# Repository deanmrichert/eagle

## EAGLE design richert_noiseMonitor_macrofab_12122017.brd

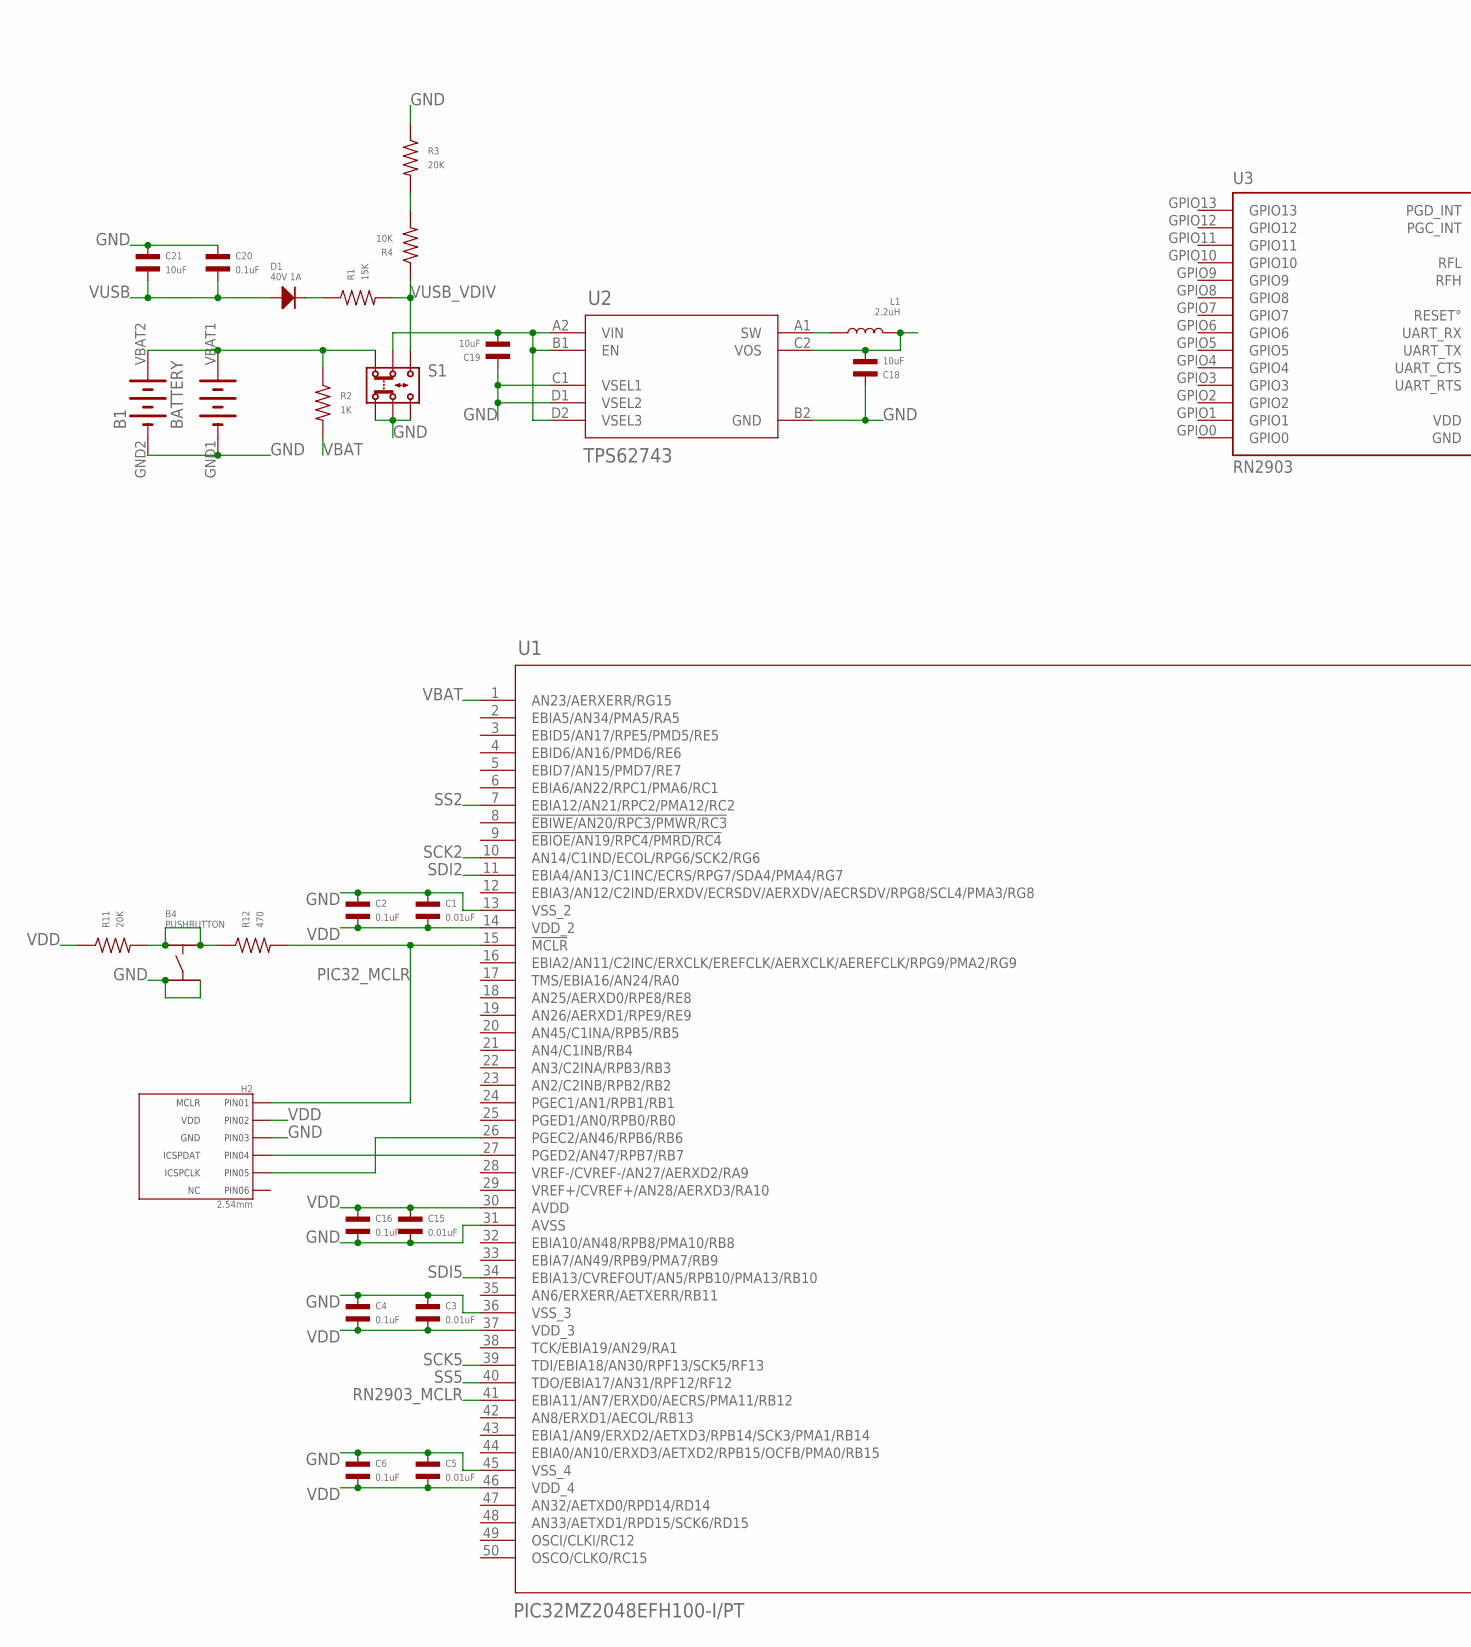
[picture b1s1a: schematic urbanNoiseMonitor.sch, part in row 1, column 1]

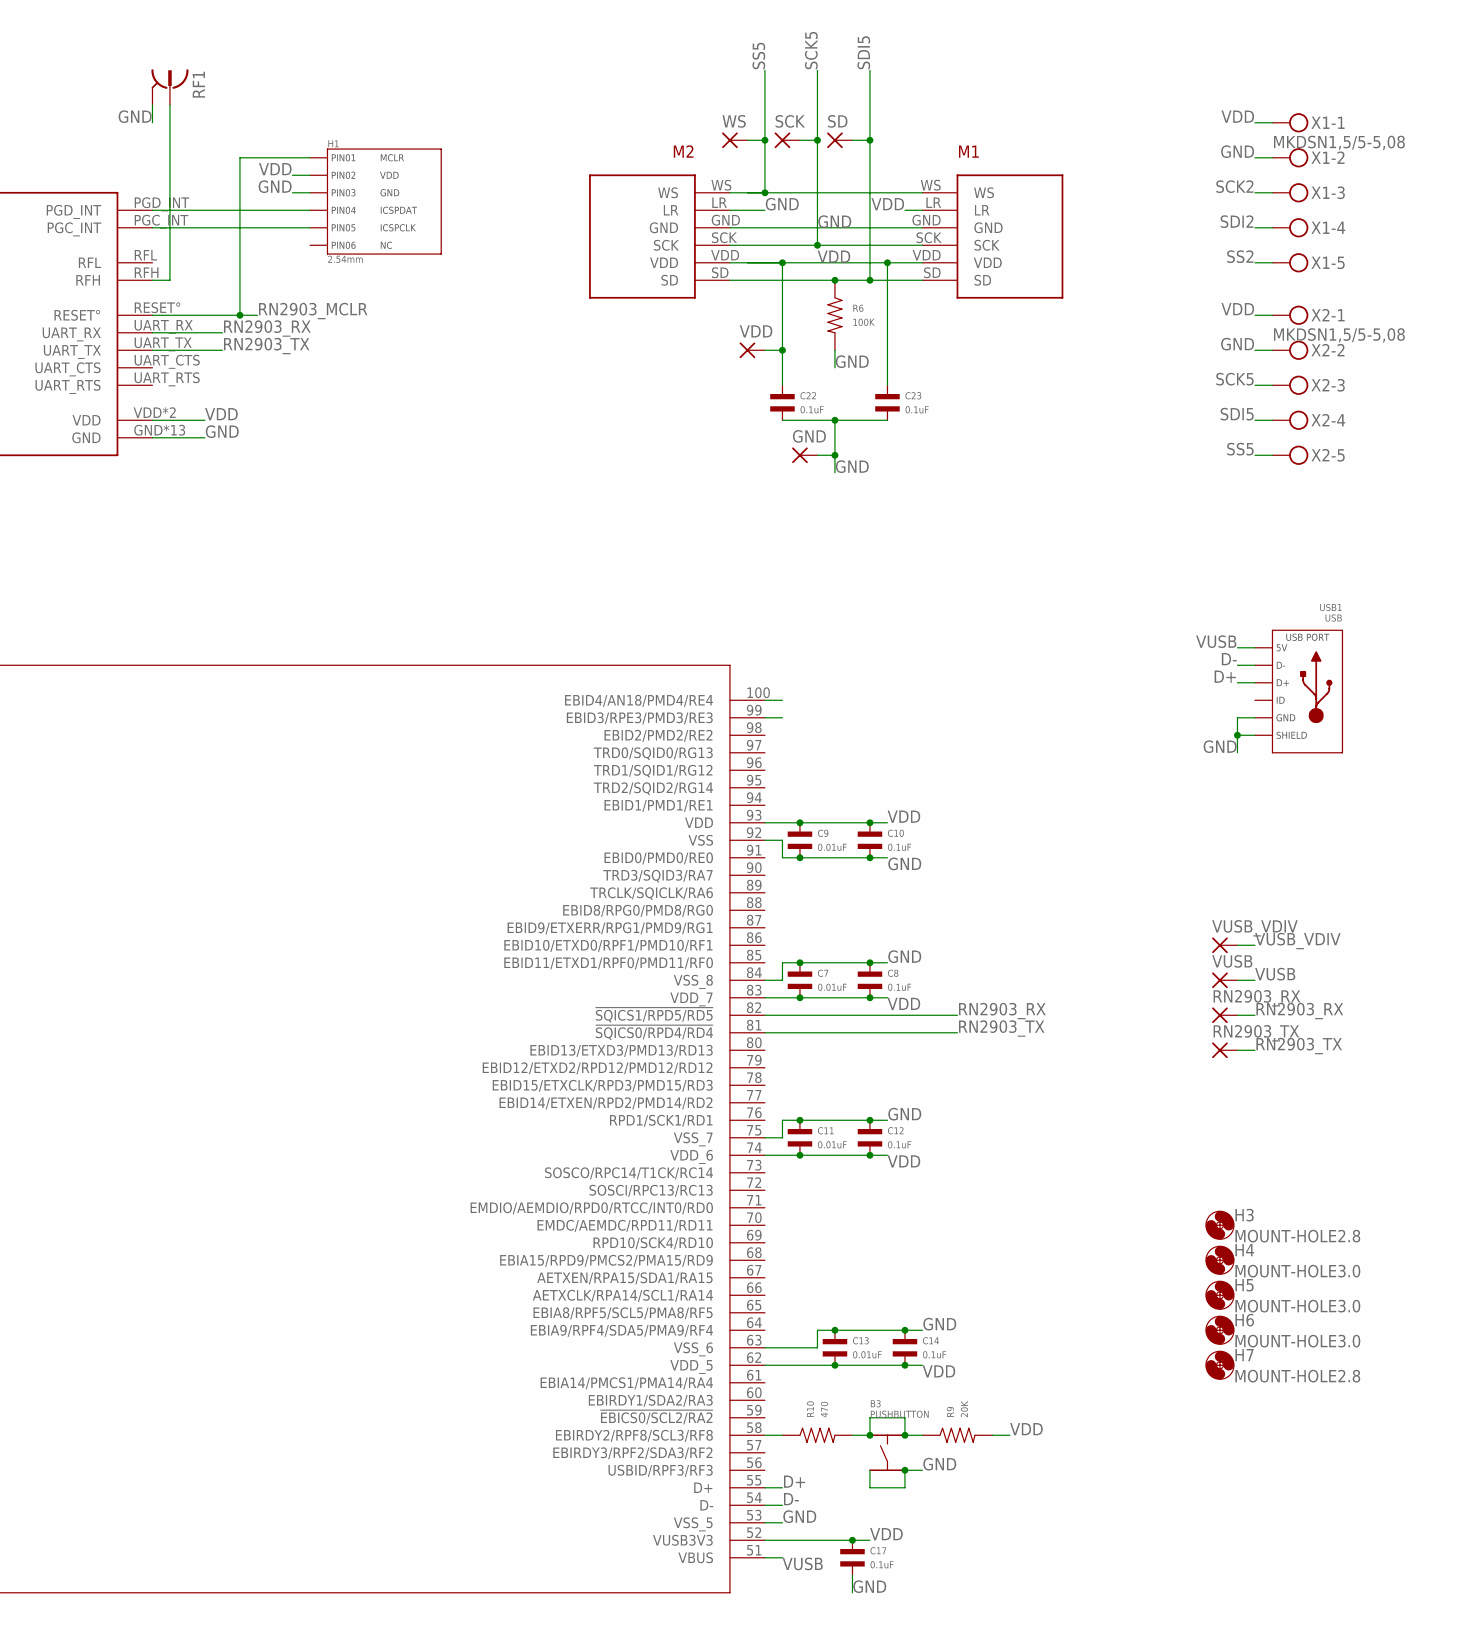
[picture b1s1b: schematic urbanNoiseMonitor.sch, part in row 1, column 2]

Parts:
B1: BATTERY; 36-2227-ND
B3, B4: PUSHBUTTON; TACT6MM
C1, C3, C5, C7, C9, C11, C13, C15: 0.01uF; C0402; MPN MF-CAP-0402-0.01uF
C2, C4, C6, C8, C10, C12, C14, C16, C17, C20, C22, C23: 0.1uF; C0402; MPN MF-CAP-0402-0.1uF
C18, C19, C21: 10uF; C1206; MPN MF-CAP-1206-10uF
D1: 40V 1A; SMA
GND: 2,54/1,0
H1, H2: 2.54mm; PTH_2.54MM_01X06
H3, H7: MOUNT-HOLE2.8; 2,8
H4, H5, H6: MOUNT-HOLE3.0; 3,0
L1: 2.2uH; L2016
M1, M2: MICROPHONE; ICS-43434
R1: 15K; R0402; MPN MF-RES-0402-15K
R2: 1K; R0402; MPN MF-RES-0402-1K
R3, R9, R11: 20K; R0805; MPN MF-RES-0805-20K
R4: 10K; R0402; MPN MF-RES-0402-10K
R6: 100K; R0402; MPN MF-RES-0402-100K
R10, R12: 470; R0402; MPN MF-RES-0402-470
RF1: SMA_JACK; J502-ND-142-0711-821/826
RN2903_RX, RN2903_TX: 2,54/1,0
S1: SLIDING_SWITCH; DPDT
SCK: 2,54/1,0
SD: 2,54/1,0
U1: PIC32MZ2048EFH100-I/PT; TQFP100_12X12MC
U2: TPS62743; YFP0008AGAC
U3: RN2903
USB1: USB; MICROUSB-RIGHT
VDD: 2,54/1,0
VUSB: 2,54/1,0
VUSB_VDIV: 2,54/1,0
WS: 2,54/1,0
X1, X2: MKDSN1,5/5-5,08; MPN 1729157

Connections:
D+: U1.55 (D+), USB1.3 (D+)
D-: U1.54 (D-), USB1.2 (D-)
GND: B1.GND1, B1.GND2, B3.P$3, B3.P$4, B4.P$3, B4.P$4, C1.P$1, C2.P$1, C3.P$1, C4.P$1, C5.P$1, C6.P$1, C7.P$1, C8.P$1, C9.P$2, C10.P$2, C11.P$1, C12.P$1, C13.P$1, C14.P$1, C15.P$2, C16.P$2, C17.P$2, C18.P$1, C19.P$1, C20.P$1, C21.P$1, C22.P$2, C23.P$2, GND.1, H1.P$3 (PIN3), H2.P$3 (PIN3), M1.GND, M2.GND, M2.LR, R3.P$1, R6.P$2, RF1.G@1 (2), RF1.G@2 (2), RF1.G@3 (2), RF1.G@4 (2), S1.1, S1.2, S1.3, U1.13 (VSS_2), U1.31 (AVSS), U1.36 (VSS_3), U1.45 (VSS_4), U1.53 (VSS_5), U1.63 (VSS_6), U1.75 (VSS_7), U1.84 (VSS_8), U1.92 (VSS), U2.B2 (GND), U2.C1 (VSEL1), U2.D1 (VSEL2), U3.GND, U3.GND1 (GND), U3.GND2 (GND), U3.GND3 (GND), U3.GND4 (GND), U3.GND5 (GND), U3.GND6 (GND), U3.GND7 (GND), U3.GND8 (GND), U3.GND9 (GND), U3.GND10 (GND), U3.GND11 (GND), U3.GND12 (GND), USB1.5 (GND), USB1.S1 (SLD), USB1.S2 (SLD), USB1.S3 (SLD), USB1.S4 (SLD), USB1.S5 (SLD), USB1.S6 (SLD), X1.2, X2.2
unnamed: L1.P$2, U2.A1 (SW)
unnamed: C19.P$2, S1.5, U2.A2 (VIN), U2.B1 (EN), U2.D2 (VSEL3)
unnamed: B1.VBAT1, B1.VBAT2, R2.P$1, S1.4
unnamed: D1.CATHODE, R1.P$1
unnamed: R3.P$2, R4.P$2
unnamed: H1.P$4 (PIN4), U3.PGD_INT
unnamed: H1.P$5 (PIN5), U3.PGC_INT
unnamed: RF1.1, U3.RFH
unnamed: B3.P$1, B3.P$2, R9.P$1, R10.P$2
unnamed: R10.P$1, U1.58 (EBIRDY2/RPF8/SCL3/RF8)
unnamed: H2.P$4 (PIN4), U1.27 (PGED2/AN47/RPB7/RB7)
unnamed: H2.P$5 (PIN5), U1.26 (PGEC2/AN46/RPB6/RB6)
unnamed: B4.P$1, B4.P$2, R11.P$2, R12.P$1
PIC32_MCLR: H2.P$1 (PIN1), R12.P$2, U1.15 (!MCLR)
RN2903_MCLR: H1.P$1 (PIN1), U1.41 (EBIA11/AN7/ERXD0/AECRS/PMA11/RB12), U3.RESET°
RN2903_RX: RN2903_RX.1, U1.82 (!SQICS1/RPD5/RD5), U3.UART_RX
RN2903_TX: RN2903_TX.1, U1.81 (!SQICS0/RPD4/RD4), U3.UART_TX
SCK2: U1.10 (AN14/C1IND/ECOL/RPG6/SCK2/RG6), X1.3
SCK5: M1.SCK, M2.SCK, SCK.1, U1.39 (TDI/EBIA18/AN30/RPF13/SCK5/RF13), X2.3
SDI2: U1.11 (EBIA4/AN13/C1INC/ECRS/RPG7/SDA4/PMA4/RG7), X1.4
SDI5: M1.SD, M2.SD, R6.P$1, SD.1, U1.34 (EBIA13/CVREFOUT/AN5/RPB10/PMA13/RB10), X2.4
SS2: U1.7 (EBIA12/AN21/RPC2/PMA12/RC2), X1.5
SS5: M1.WS, M2.WS, U1.40 (TDO/EBIA17/AN31/RPF12/RF12), WS.1, X2.5
VBAT: R2.P$2, U1.1 (AN23/AERXERR/RG15)
VDD: C1.P$2, C2.P$2, C3.P$2, C4.P$2, C5.P$2, C6.P$2, C7.P$2, C8.P$2, C9.P$1, C10.P$1, C11.P$2, C12.P$2, C13.P$2, C14.P$2, C15.P$1, C16.P$1, C17.P$1, C18.P$2, C22.P$1, C23.P$1, H1.P$2 (PIN2), H2.P$2 (PIN2), L1.P$1, M1.LR, M1.VDD, M2.VDD, R9.P$2, R11.P$1, U1.14 (VDD_2), U1.30 (AVDD), U1.37 (VDD_3), U1.46 (VDD_4), U1.52 (VUSB3V3), U1.62 (VDD_5), U1.74 (VDD_6), U1.83 (VDD_7), U1.93 (VDD), U2.C2 (VOS), U3.VDD, U3.VDD2 (VDD), VDD.1, X1.1, X2.1
VUSB: C20.P$2, C21.P$2, D1.ANODE, U1.51 (VBUS), USB1.1 (5V), VUSB.1
VUSB_VDIV: R1.P$2, R4.P$1, S1.6, VUSB_VDIV.1

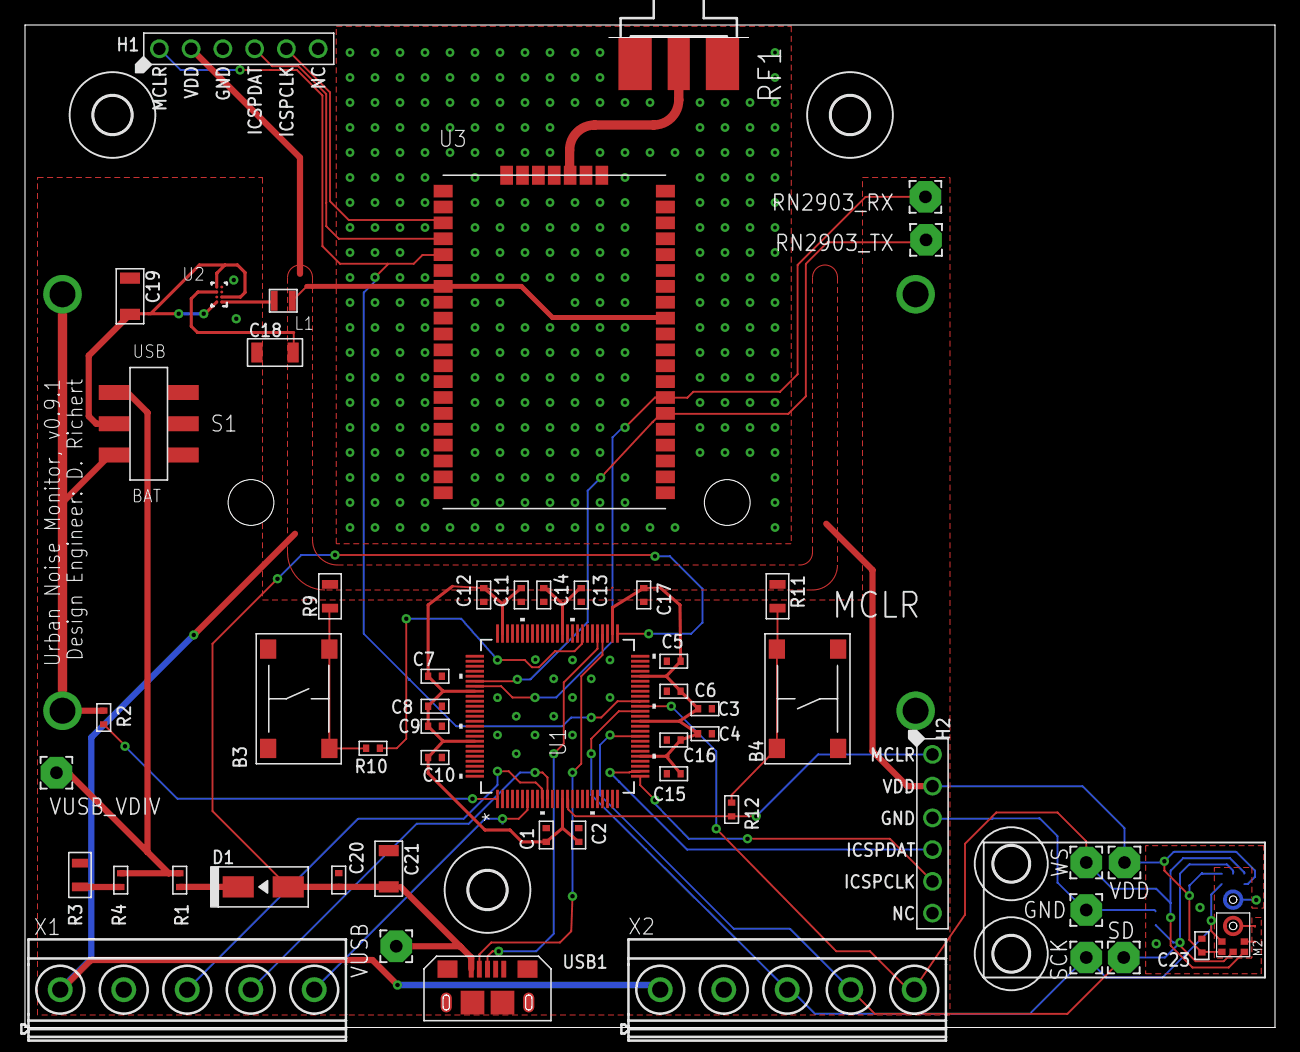
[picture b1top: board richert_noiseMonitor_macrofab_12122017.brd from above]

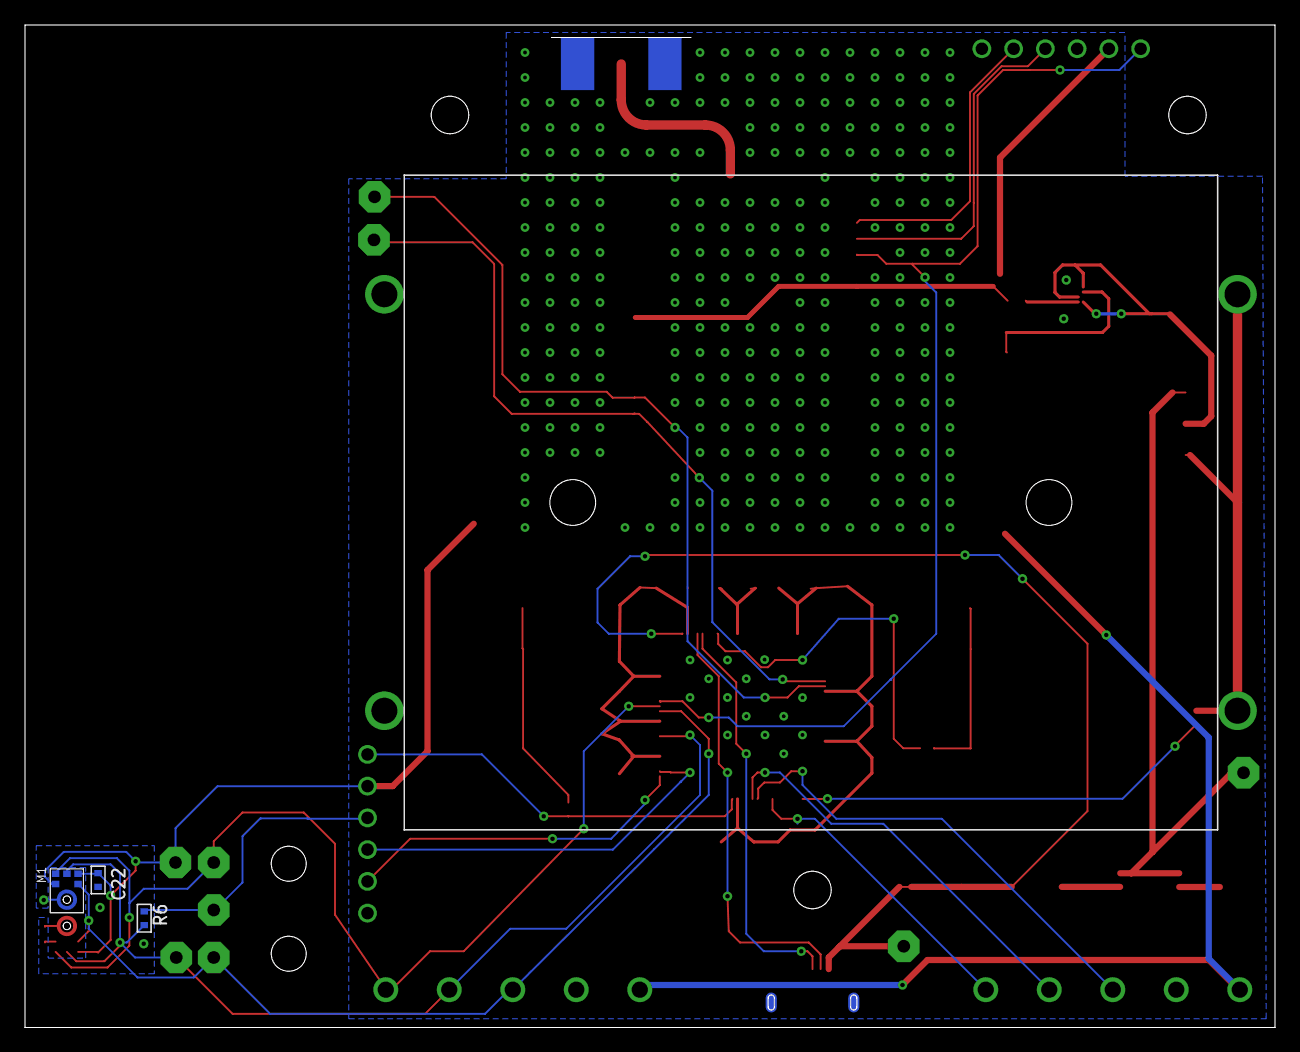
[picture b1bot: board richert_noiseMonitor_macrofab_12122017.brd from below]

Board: 2 copper layers, 100.0 x 80.2 mm, 63 parts (3 on the bottom side), 30 nets.

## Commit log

2017-12-14 created license
2017-12-14 moved files to urbanNoiseMonitor folder
